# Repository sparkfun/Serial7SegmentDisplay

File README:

Serial 7-Segment Display v2
5/12/10
Spark Fun Electronics
by: Jim Lindblom

License: Creative Commons Attribution Share-Alike 3.0
http://creativecommons.org/licenses/by-sa/3.0

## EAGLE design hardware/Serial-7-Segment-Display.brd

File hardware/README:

////////////////////////////////
/// Serial 7-Segment Display ///
////////////////////////////////
/// PCB Design Files ///////////
////////////////////////////////

These files were created with Eagle 6.1.0.
Serial-7-Segment-Display.sch: Schematic
Serial-7-Segment-Display.brd: PCB Design

This project is Open-source Hardware!

License: Creative Commons Attribution-ShareAlike 3.0 (CC BY-SA 3.0)
http://creativecommons.org/licenses/by-sa/3.0/

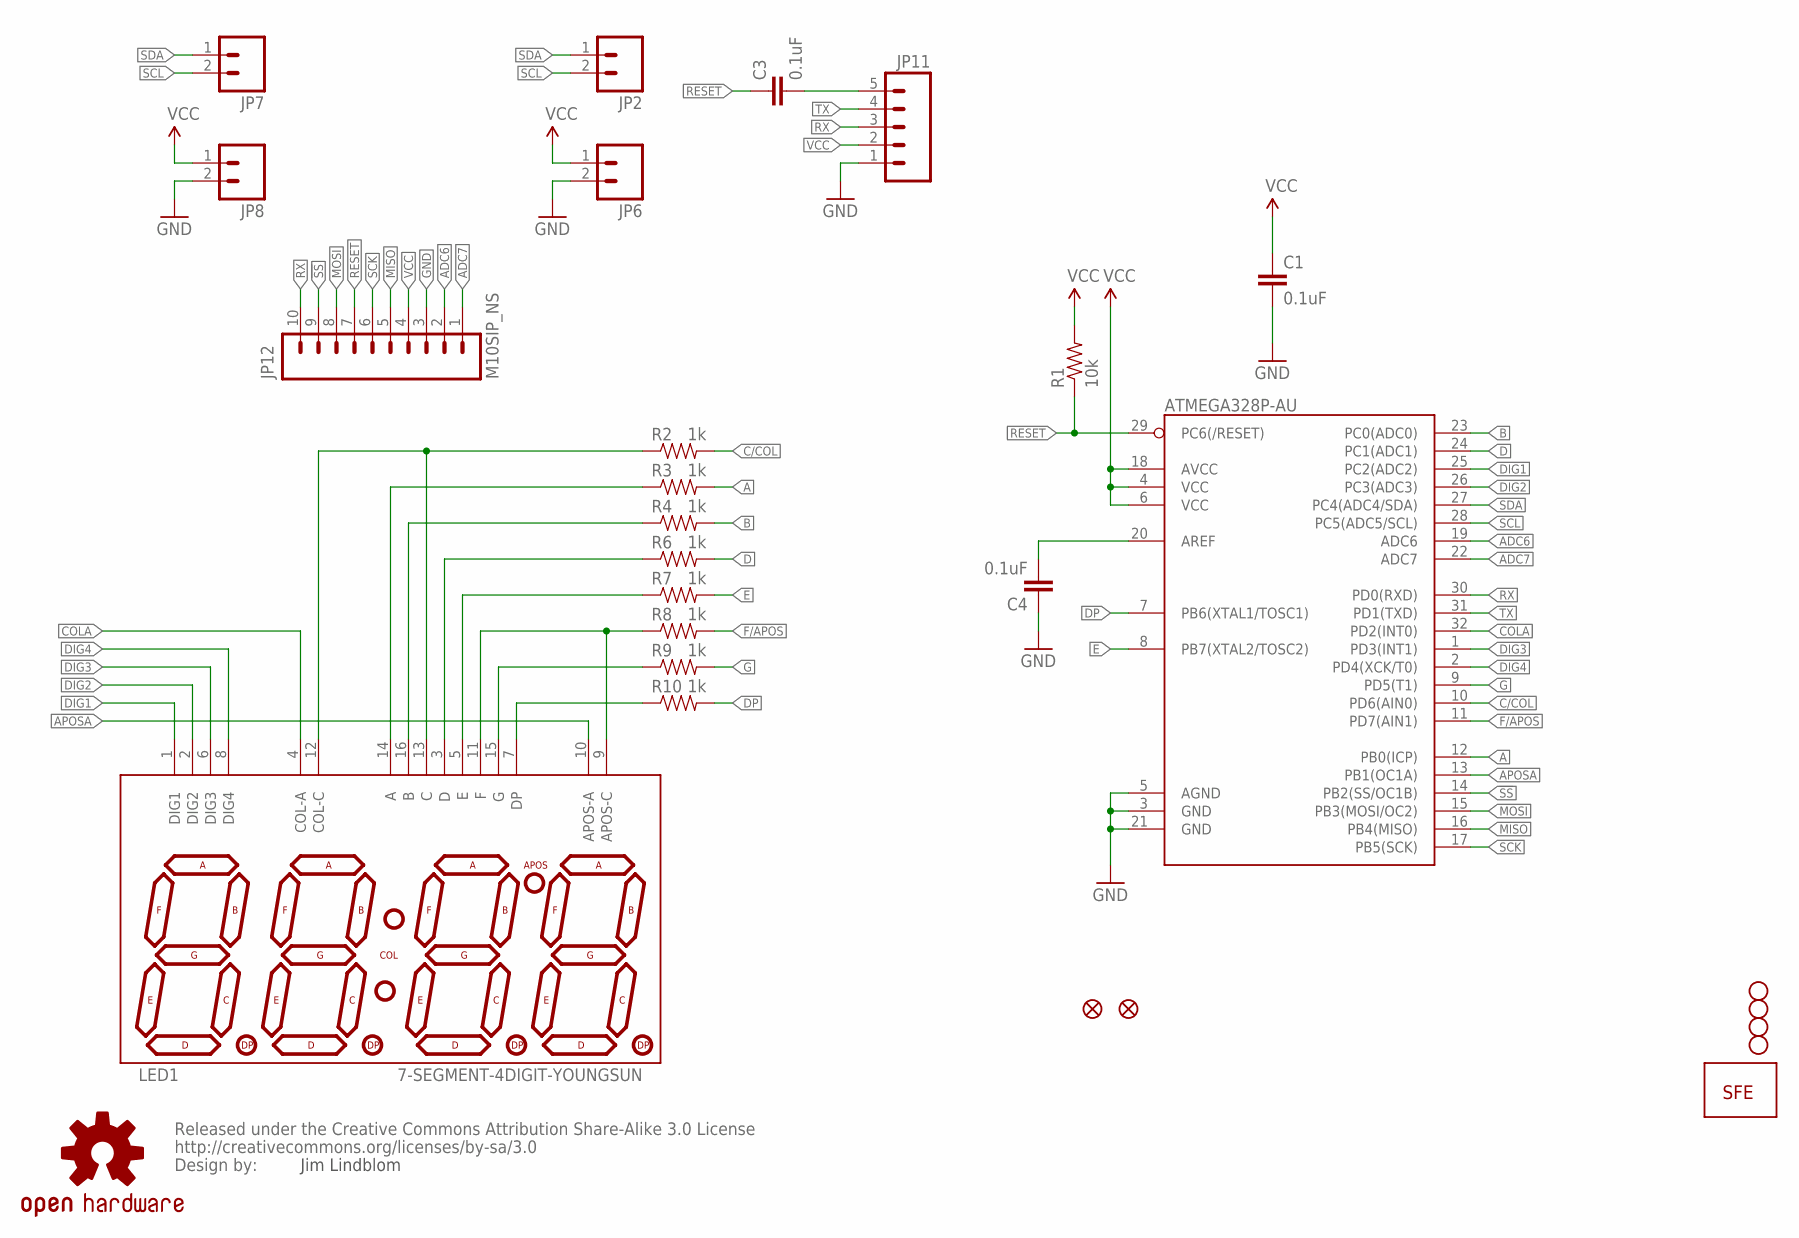
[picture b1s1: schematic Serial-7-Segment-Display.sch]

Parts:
ATMEGA328P-AU: ATMEGA328P-AU; TQFP32-08
C1, C3, C4: 0.1uF; 0402-CAP
JP1, JP3, JP4, JP5: STAND-OFF
JP2, JP6, JP7, JP8: M021X02_NO_SILK; 1X02_NO_SILK
JP9, JP10: FIDUCIALUFIDUCIAL; MICRO-FIDUCIAL
JP11: M05PTH-NS; 1X05_NO_SILK
JP12: M10SIP_NS; 1X10_NO_SILK
LED1: 7-SEGMENT-4DIGIT-YOUNGSUN
R1: 10k; 0402-RES
R2, R3, R4, R6, R7, R8, R9, R10: 1k; 0402-RES
U$1: CREATIVE_COMMONS
U$2: LOGO-SFESK; SFE-LOGO-FLAME
U$4: OSHW-LOGOS; OSHW-LOGO-S

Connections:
!SS: ATMEGA328P-AU.14 (PB2(SS/OC1B)), JP12.9
A: ATMEGA328P-AU.12 (PB0(ICP)), R3.2
ADC6: ATMEGA328P-AU.19 (ADC6), JP12.2
ADC7: ATMEGA328P-AU.22 (ADC7), JP12.1
APOSA: ATMEGA328P-AU.13 (PB1(OC1A)), LED1.10 (APOS-A)
B: ATMEGA328P-AU.23 (PC0(ADC0)), R4.2
C/COL: ATMEGA328P-AU.10 (PD6(AIN0)), R2.2
COLA: ATMEGA328P-AU.32 (PD2(INT0)), LED1.4 (COL-A)
D: ATMEGA328P-AU.24 (PC1(ADC1)), R6.2
DIG1: ATMEGA328P-AU.25 (PC2(ADC2)), LED1.1 (DIG1)
DIG2: ATMEGA328P-AU.26 (PC3(ADC3)), LED1.2 (DIG2)
DIG3: ATMEGA328P-AU.1 (PD3(INT1)), LED1.6 (DIG3)
DIG4: ATMEGA328P-AU.2 (PD4(XCK/T0)), LED1.8 (DIG4)
DP: ATMEGA328P-AU.7 (PB6(XTAL1/TOSC1)), R10.2
E: ATMEGA328P-AU.8 (PB7(XTAL2/TOSC2)), R7.2
F/APOS: ATMEGA328P-AU.11 (PD7(AIN1)), R8.2
G: ATMEGA328P-AU.9 (PD5(T1)), R9.2
GND: ATMEGA328P-AU.3 (GND), ATMEGA328P-AU.5 (AGND), ATMEGA328P-AU.21 (GND), C1.2, C4.1, JP6.2, JP8.2, JP11.1, JP12.3
MISO: ATMEGA328P-AU.16 (PB4(MISO)), JP12.5
MOSI: ATMEGA328P-AU.15 (PB3(MOSI/OC2)), JP12.8
unnamed: ATMEGA328P-AU.20 (AREF), C4.2
unnamed: LED1.7 (DP), R10.1
unnamed: LED1.15 (G), R9.1
unnamed: LED1.9 (APOS-C), LED1.11 (F), R8.1
unnamed: LED1.5 (E), R7.1
unnamed: LED1.3 (D), R6.1
unnamed: LED1.16 (B), R4.1
unnamed: LED1.14 (A), R3.1
unnamed: LED1.12 (COL-C), LED1.13 (C), R2.1
unnamed: C3.2, JP11.5
RESET: ATMEGA328P-AU.29 (PC6(/RESET)), C3.1, JP12.7, R1.1
RX: ATMEGA328P-AU.30 (PD0(RXD)), JP11.3, JP12.10
SCK: ATMEGA328P-AU.17 (PB5(SCK)), JP12.6
SCL: ATMEGA328P-AU.28 (PC5(ADC5/SCL)), JP2.2, JP7.2
SDA: ATMEGA328P-AU.27 (PC4(ADC4/SDA)), JP2.1, JP7.1
TX: ATMEGA328P-AU.31 (PD1(TXD)), JP11.4
VCC: ATMEGA328P-AU.4 (VCC), ATMEGA328P-AU.6 (VCC), ATMEGA328P-AU.18 (AVCC), C1.1, JP6.1, JP8.1, JP11.2, JP12.4, R1.2

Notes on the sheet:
Jim Lindblom

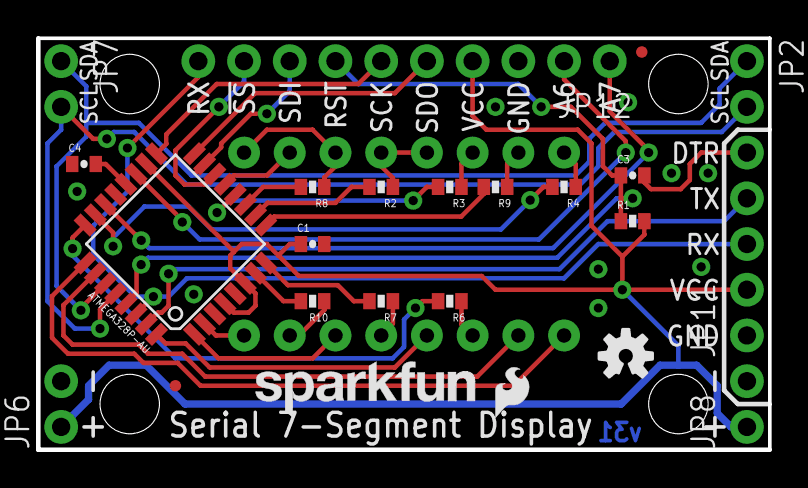
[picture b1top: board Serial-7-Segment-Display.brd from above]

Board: 2 copper layers, 40.6 x 22.9 mm, 30 parts (1 on the bottom side), 37 nets.

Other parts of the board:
U$3: LOGO-SFENW2; SFE-NEW-WEB

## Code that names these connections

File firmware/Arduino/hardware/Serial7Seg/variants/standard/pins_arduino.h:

/*
  pins_arduino.h - Pin definition functions for Arduino
  Part of Arduino - http://www.arduino.cc/

  Copyright (c) 2007 David A. Mellis

  This library is free software; you can redistribute it and/or
  modify it under the terms of the GNU Lesser General Public
  License as published by the Free Software Foundation; either
  version 2.1 of the License, or (at your option) any later version.

  This library is distributed in the hope that it will be useful,
  but WITHOUT ANY WARRANTY; without even the implied warranty of
  MERCHANTABILITY or FITNESS FOR A PARTICULAR PURPOSE.  See the GNU
  Lesser General Public License for more details.

  You should have received a copy of the GNU Lesser General
  Public License along with this library; if not, write to the
  Free Software Foundation, Inc., 59 Temple Place, Suite 330,
  Boston, MA  02111-1307  USA

  $Id: wiring.h 249 2007-02-03 16:52:51Z mellis $
*/

#ifndef Pins_Arduino_h
#define Pins_Arduino_h

#include <avr/pgmspace.h>

#define NUM_DIGITAL_PINS            22
#define NUM_ANALOG_INPUTS           8
#define analogInputToDigitalPin(p)  ((p < 6) ? (p) + 14 : -1)

#if defined(__AVR_ATmega8__)
#define digitalPinHasPWM(p)         ((p) == 9 || (p) == 10 || (p) == 11)
#else
#define digitalPinHasPWM(p)         ((p) == 3 || (p) == 5 || (p) == 6 || (p) == 9 || (p) == 10 || (p) == 11)
#endif

static const uint8_t SS   = 10;
static const uint8_t MOSI = 11;
static const uint8_t MISO = 12;
static const uint8_t SCK  = 13;

static const uint8_t SDA = 18;
static const uint8_t SCL = 19;
static const uint8_t LED_BUILTIN = 13;

static const uint8_t A0 = 14;
static const uint8_t A1 = 15;
static const uint8_t A2 = 16;
static const uint8_t A3 = 17;
static const uint8_t A4 = 18;
static const uint8_t A5 = 19;
static const uint8_t A6 = 20;
static const uint8_t A7 = 21;

#define digitalPinToPCICR(p)    (((p) >= 0 && (p) <= 21) ? (&PCICR) : ((uint8_t *)0))
#define digitalPinToPCICRbit(p) (((p) <= 7) ? 2 : (((p) <= 13) ? 0 : 1))
#define digitalPinToPCMSK(p)    (((p) <= 7) ? (&PCMSK2) : (((p) <= 13) ? (&PCMSK0) : (((p) <= 21) ? (&PCMSK1) : ((uint8_t *)0))))
#define digitalPinToPCMSKbit(p) (((p) <= 7) ? (p) : (((p) <= 13) ? ((p) - 8) : ((p) - 14)))

#ifdef ARDUINO_MAIN

// On the Arduino board, digital pins are also used
// for the analog output (software PWM).  Analog input
// pins are a separate set.

// ATMEL ATMEGA8 & 168 / ARDUINO
//
//                  +-\/-+
//            PC6  1|    |28  PC5 (AI 5)
//      (D 0) PD0  2|    |27  PC4 (AI 4)
//      (D 1) PD1  3|    |26  PC3 (AI 3)
//      (D 2) PD2  4|    |25  PC2 (AI 2)
// PWM+ (D 3) PD3  5|    |24  PC1 (AI 1)
//      (D 4) PD4  6|    |23  PC0 (AI 0)
//            VCC  7|    |22  GND
//            GND  8|    |21  AREF
//            PB6  9|    |20  AVCC
//            PB7 10|    |19  PB5 (D 13)
// PWM+ (D 5) PD5 11|    |18  PB4 (D 12)
// PWM+ (D 6) PD6 12|    |17  PB3 (D 11) PWM
//      (D 7) PD7 13|    |16  PB2 (D 10) PWM
//      (D 8) PB0 14|    |15  PB1 (D 9) PWM
//                  +----+
//
// (PWM+ indicates the additional PWM pins on the ATmega168.)

// ATMEL ATMEGA1280 / ARDUINO
//
// 0-7 PE0-PE7   works
// 8-13 PB0-PB5  works
// 14-21 PA0-PA7 works 
// 22-29 PH0-PH7 works
// 30-35 PG5-PG0 works
// 36-43 PC7-PC0 works
// 44-51 PJ7-PJ0 works
// 52-59 PL7-PL0 works
// 60-67 PD7-PD0 works
// A0-A7 PF0-PF7
// A8-A15 PK0-PK7


// these arrays map port names (e.g. port B) to the
// appropriate addresses for various functions (e.g. reading
// and writing)
const uint16_t PROGMEM port_to_mode_PGM[] = {
	NOT_A_PORT,
	NOT_A_PORT,
	(uint16_t) &DDRB,
	(uint16_t) &DDRC,
	(uint16_t) &DDRD,
};

const uint16_t PROGMEM port_to_output_PGM[] = {
	NOT_A_PORT,
	NOT_A_PORT,
	(uint16_t) &PORTB,
	(uint16_t) &PORTC,
	(uint16_t) &PORTD,
};

const uint16_t PROGMEM port_to_input_PGM[] = {
	NOT_A_PORT,
	NOT_A_PORT,
	(uint16_t) &PINB,
	(uint16_t) &PINC,
	(uint16_t) &PIND,
};

const uint8_t PROGMEM digital_pin_to_port_PGM[] = {
	PD, /* 0 */
	PD,
	PD,
	PD,
	PD,
	PD,
	PD,
	PD,
	PB, /* 8 */
	PB,
	PB,
	PB,
	PB,
	PB,
	PC, /* 14 */
	PC,
	PC,
	PC,
	PC,
	PC,
	PC,
	PC,
	PB, /* 20 PB6 */
	PB,	// PB7
};

const uint8_t PROGMEM digital_pin_to_bit_mask_PGM[] = {
	_BV(0), /* 0, port D */
	_BV(1),
	_BV(2),
	_BV(3),
	_BV(4),
	_BV(5),
	_BV(6),
	_BV(7),
	_BV(0), /* 8, port B */
	_BV(1),
	_BV(2),
	_BV(3),
	_BV(4),
	_BV(5),
	_BV(0), /* 14, port C */
	_BV(1),
	_BV(2),
	_BV(3),
	_BV(4),
	_BV(5),
	_BV(6),
	_BV(7),	
	_BV(6),	// PB6
	_BV(7),	// PB7
};

const uint8_t PROGMEM digital_pin_to_timer_PGM[] = {
	NOT_ON_TIMER, /* 0 - port D */
	NOT_ON_TIMER,
	NOT_ON_TIMER,
	// on the ATmega168, digital pin 3 has hardware pwm
#if defined(__AVR_ATmega8__)
	NOT_ON_TIMER,
#else
	TIMER2B,
#endif
	NOT_ON_TIMER,
	// on the ATmega168, digital pins 5 and 6 have hardware pwm
#if defined(__AVR_ATmega8__)
	NOT_ON_TIMER,
	NOT_ON_TIMER,
#else
	TIMER0B,
	TIMER0A,
#endif
	NOT_ON_TIMER,
	NOT_ON_TIMER, /* 8 - port B */
	TIMER1A,
	TIMER1B,
#if defined(__AVR_ATmega8__)
	TIMER2,
#else
	TIMER2A,
#endif
	NOT_ON_TIMER,
	NOT_ON_TIMER,
	NOT_ON_TIMER,
	NOT_ON_TIMER, /* 14 - port C */
	NOT_ON_TIMER,
	NOT_ON_TIMER,
	NOT_ON_TIMER,
	NOT_ON_TIMER,
	NOT_ON_TIMER,
	NOT_ON_TIMER,
	NOT_ON_TIMER,
	NOT_ON_TIMER,
};

#endif

#endif

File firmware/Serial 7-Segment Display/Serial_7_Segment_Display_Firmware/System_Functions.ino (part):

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  //This pinout is for the original Serial7Segment layout
  //-=-=-=-=-=-=-=-=-=-=-=-=-=-=-=-=-=-=-=-=-=-=-=-=-=-=-=-=-=-=-=-=-=-=-
#if DISPLAY_TYPE == S7S
  int digit1 = 16; // DIG1 = A2/16 (PC2)
  int digit2 = 17; // DIG2 = A3/17 (PC3)
  int digit3 = 3;  // DIG3 = D3 (PD3)
  int digit4 = 4;  // DIG4 = D4 (PD4)

  //Declare what pins are connected to the segments
  int segA = 8;  // A = D8 (PB0)
  int segB = 14; // B = A0 (PC0)
  int segC = 6;  // C = D6 (PD6), shares a pin with colon cathode
  int segD = A1; // D = A1 (PC1)
  int segE = 23; // E = PB7 (not a standard Arduino pin: Must add PB7 as digital pin 23 to pins_arduino.h)
  int segF = 7;  // F = D7 (PD6), shares a pin with apostrophe cathode
  int segG = 5;  // G = D5 (PD5)
  int segDP= 22; //DP = PB6 (not a standard Arduino pin: Must add PB6 as digital pin 22 to pins_arduino.h)

  int digitColon = 2; // COL-A = D2 (PD2) (anode of colon)
  int segmentColon = 6; // COL-C = D6 (PD6) (cathode of colon), shares a pin with C
  int digitApostrophe = 9; // APOS-A = D9 (PB1) (anode of apostrophe)
  int segmentApostrophe = 7; // APOS-C = D7 (PD7) (cathode of apostrophe), shares a pin with F

  int numberOfDigits = 4; //Do you have a 2 or 4 digit display?

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  //This pinout is for the original Serial 7 Segment Shield
  //-=-=-=-=-=-=-=-=-=-=-=-=-=-=-=-=-=-=-=-=-=-=-=-=-=-=-=-=-=-=-=-=-=-=-
#if DISPLAY_TYPE == S7SHIELD
  int digit1 = 16; // DIG1 = A2/16 (PC2)
  int digit2 = 17; // DIG2 = A3/17 (PC3)
  int digit3 = 3;  // DIG3 = D3 (PD3)
  int digit4 = 4;  // DIG4 = D4 (PD4)

  //Declare what pins are connected to the segments
  int segA = 8;  // A = D8 (PB0)
  int segB = 14; // B = A0 (PC0)
  int segC = 6;  // C = D6 (PD6), shares a pin with colon cathode
  int segD = A1; // D = A1 (PC1)
  int segE = 23; // E = PB7 (not a standard Arduino pin: Must add PB7 as digital pin 23 to pins_arduino.h)
  int segF = 7;  // F = D7 (PD6), shares a pin with apostrophe cathode
  int segG = 5;  // G = D5 (PD5)
  int segDP= 22; //DP = PB6 (not a standard Arduino pin: Must add PB6 as digital pin 22 to pins_arduino.h)

  int numberOfDigits = 4; //Do you have a 2 or 4 digit display?

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#if DISPLAY_TYPE == OPENSEGMENT
  //See if any solder jumpers have been closed

  //Arduino doesn't really support PB6 and PB7 and GPIOs (normally the 16MHz
  //crystal is there) so let's do it the old school way
  //digitalWrite(JUMPER_COUNTER, HIGH); //Enable internal pullup
  //pinMode(JUMPER_METER, INPUT_PULLUP);
  
  DDRB &= 0b00111111; //Set PB7 and PB6 to inputs
  PORTB |= 0b11000000; //Enable external pull ups
  
  Serial.println("Jumper check:");
  if( (PINB & 1<<6) == 0) //If counter pin is low
  {
    deviceMode = MODE_COUNTER;
    Serial.println("PB6 jumper closed");
  }
  else if( (PINB & 1<<7) == 0) //digitalRead(JUMPER_METER) == LOW)
  {
    deviceMode = MODE_ANALOG;
    Serial.println("PB7 jumper closed");
  }
#endif

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
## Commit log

2010-09-01 Original source code commit.
2010-09-01 Original source code files
2010-09-01 Added a README to project folder
2010-09-13 Lots of quick, minimal fixes. Lots more to come! -------------------------------------------- - Reorganized main.c and Serial-7-Seg.h. Only function prototypes, defines, and includes are in the .h fi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
    - Optimized a few of the global variable types and made volatile where necessary.
    - Got rid of a silly 1 argument switch statement.
2012-09-06 Version 3.0: Massive overhaul of the code. Added I2C Functionality. Added commands to better support I2C. Added buffering to serial inputs. The hardware has changed, pins have moved, current limiting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
2012-09-06 Cleaning up directory structure. Adding a couple README's.
2012-10-07 Renamed INO file for easier use. Fixed typos and white space.
    Arduino has to have the file name same as directory. Removed version
    number from file. Repo should be able to handle file versions.
2012-10-07 Changed file extensions for easier editing.
2012-10-21 Now uses SevSeg library for support of multiple types of displays.
    SevSeg library supports both common anode and cathode. Please test. From
    here, I plan to make many smaller firmware changes (that do not related
    to how segments are actually displayed).
    I need to get the products with a ATmega type backpack (Serial7Segment
    and OpenSegment) to this library so that we can use similar code, but
    with different pin definitions.
2012-10-21 Moved SPI pins to #defines.
2012-10-31 Added a very simple serial example.
2012-10-31 Changed comments from /* to // to fit the SparkFun guidelines.
    This is nothing but whitespace changes.
2012-10-31 Added RX pin factory reset feature. Moved away from hardware UART setup.
    Many changes but the major one was adding the ability to reset the UART
    to 9600 when the RX is pulled low for a certain amount of time. This
    affected boot up, EEPROM locations, and the way that the UART is
    controlled. We now initialize the UART using standard Arduino calls
    instead of hardware registers. This commit works well with the
    BasicSerial example code. Even though there are quite a few code
2012-10-31 Reverting to the latest working version
    All commits after this use the SevSeg library to control the display and
    do not work with the display at the moment. As these displays are
    beginning to go live, I'd like a working version only of the code to be
    hosted here.
2012-10-31 Reverting to older, working, non SevSeg version
2012-11-02 Moved display init into function. Removed readSettings.
    I realized that the EEPROM locations are read during each 'setupTWI',
    'setupUART' function so I removed the readSystemSettings and left the
    EEPROM checking where it originally was. The display init is now in its
    own function (also where we look up brightness setting).
2012-11-02 Moved display init into its own function.
2012-11-02 Added support for display brightness and example sketch.
    I added brightness support to the SevSeg library. I'm fairly happy with
    it. Works well with the OpenSegment backpack. I need to get a S7S
    backpack for testing as well.
2012-11-02 Example sketch to show variable brightness control.
2012-11-02 Now uses SetBrightness command.
    User supplies value from 0 to 100 percent instead of 0 to 255.
    SetBrightness does all the error correcting and map to get to
    delayMicrosecond value.
2012-11-02 Adding additional baud rate levels.
    I didn't realize there was 76800 and 38400bps in there. They're back in
    there now.
2012-11-02 Added I2C interface example.
    Added a really simple I2C example sketch. Cleaned up some residual stuff
    in the main firmware. Moved the I2C receive event down below the main
    loop because it's not really an ISR.
2012-11-02 Added I2C brightness control sketch.
2012-11-03 Added SPI example sketches. Renamed files.
    Added basic SPI control and SPI control of settings. Works well. Also
    re-named some of the examples to make it more clear
2012-11-05 Addded different comments to show the mapping of PB6 and PB7.
    To use the additional pins, PB6 and PB7, on the ATmega328 we have to add
    some maps to the pins_arduino.h file. This allows Arduino to identify
    PB6 and digital pin 22, and PB7 as digital pin 23.
2012-11-05 Added support for Serial7Segment hardware. Added colon/apos example.
    Code should now work on Serial7Segment hardware directly. Use the
    Serial_ColonDots example sketch to test it.
2012-11-05 Improved the software reset sketch. Uses strings now.
2012-11-05 Experimenting with volt meter display.
    Works well. Not sure where to put the A/D checking. Not in the main
    loop. Perhaps a dedicated function where we only go if a jumper is
    closed.
2012-11-22 Added Predator segment control example.
2012-11-22 Removing old test code.
2012-11-22 Removed analog feature in order to try to unite branches.
2012-11-24 First add of multimode capability.
    Not fully tested but somewhat working.
2012-11-24 Completed multimode support.
    Works well. Split the bulkier system functions into their own file. This
    made room for the mode runctions in the main file.
2012-11-24 Completed multimode support.
2012-11-26 Corrected a bad bug. Tested with new SevSeg library.
    I moved commandMode variable into the updateBufferData because I didn't
    think it was used anywhere else. The variable is not used anywhere else,
    but the function depends on the command being stored towards the end of
    the function. Summary: commandMode needs to be global. This fixes my
    mistake.
2012-11-26 Corrected so that we default to data mode.
2013-01-01 Corrected device mode bug and library init bug.
    Device mode has to be an unsigned char because upon first power up the
    EEPROM is 0xFF (-1 or 255). The 1" displays are common cathode but with
    the PNP/NPN configuration of OpenSegment, it actually inverts the
    signals so we need to use common anode to get the library to work.
2013-01-10 Renamed the Mode_Change example to Serial_Mode_Change.
2013-02-13 fixed some comments, re-worked pin labels in sch.
    Fixed comments in System_Functions.ino which mapped Arduino pins to
    display pins
    Some labels on the schematic did not match the display pin they
    connected to. Renamed those nets to make more sense.
    Added a pdf of current schematic, not sure if this'll be sustainable.
    Trying it out.
2013-03-08 migrate readme to markdown, add image/links, product versions, dir contents
2013-03-18 Added checks on PB6/PB7 on OpenSegment hardware.
    Checks to see if jumpers are closed on PB6/PB7 and sets mode to counter
    or analog meter appropriately.
2013-05-03 Added 7 segment shield as an option to the firmware.
2014-03-13 Adding link to SevSeg library
2015-02-14 Adding 7-bit I2C warning to example code. Added fast I2C example.
    OpenSegment works at 400kHz! Neat!
2015-05-14 Fixing variant - should be ser7seg, not standard.
2015-05-14 Renaming pins_arduino.h folder to ser7seg.
2015-05-14 hardware addon structure to matches 1.6 standards
    Added platform.txt
    Added necessary entries boards.txt
    Buried addon files in /hardware/sparkfun/avr/
2015-06-11 Added example on how to change I2C address
2015-12-18 created larger panel v31b
2016-01-14 TimeOut for commands added
2016-01-21 Adding check during reset to avoid skipping brightness value.
2017-02-13 Removed Arduino board support and change README to point users to the support in the Arduino_Boards repository.
2024-02-29 updates firmware to support SegSev 3.7.0
    This old firmware is designed to be used with a separately maintained
    and released fork of SegSev and the APIs now appear to differ.
    These updates address this by updating various calls to the new API
    and making the necessary refresh calls.
    This change is probably useful for others since folks using library
    managers will likely end up with the other version.
2025-06-27 Update README.md
    Updating link

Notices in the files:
firmware/Serial 7-Segment Display/Serial_7_Segment_Display_Firmware/System_Functions.ino:
See main file for license and information.
parts and their libraries:
SparkFun-Electromechanical: Licensing: CC v3.0 Share-Alike You are welcome to use this library for commercial purposes.
SparkFun-Retired: Licensing:Creative Commons ShareAlike 4.0 International - https://creativecommons.org/licenses/by-sa/4.0
